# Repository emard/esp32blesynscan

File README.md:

# ESP32 blesyncscan

Micropython ESP32, ESP32S3, ESP32C3 Bluetooth Low Energy (BLE)
Motor server, WiFi Motor Server and USB-WiFi Motor Client for
SynScan Pro on Windows, Linux, Android.
Arduino ESP32 Bluetooth Classic UART bridge for SynScan Pro
under Wine on Linux.
UART 3.3V TTL is connected to SkyWatcher Virtuoso Mini
or Virtuoso GTi mount.

ESP32C3 USB-C port can be used as direct USB-SERIAL on PC
connected to Motor over wire or remote USB-SERIAL over WiFi.

Do not use this to upgrade Motor firmware.
Motor firmware should be upgraded over wire using
USB-SERIAL UART 3.3V TTL based on PL2303 or FT232R chip.

# Install

"micropython" directory contains latest developent.
To install, continue with micropython/README.md

"Arduino" directory contains old code which should be
upgraded with features micropython code has.
To install, continue with Arduino/README.md

Bluetooth Classic is available only for Arduino.
Micropython doesn't support Bluetooth Classic.

# Electrical

There should be 12V->3.3V converter.
To save power recommended is switching converter 
(Canton Power or RECOM).
RJ-12 plug can't guarantee that GND makes
connection before 12V pin. Hot-plugging
can apply 12V to 3.3V pins and risk a
permanent damage. Avoid hot-plugging.

On the mount "Virtuoso Mini" RX and TX are labeled
swapped and seems as wired together making it a
half-duplex serial port and ESP32 should cancel echo.
ESP32 TX line should "simulate" open collector
output with a resistor 10k and small low drop diode
BAT42.

On the mount "Virtuoso GTi" RX and TX are labeled
normal and are not wired together making it a
full-duplex serial port without echo.
ESP32 TX line should connect directly to ESP32.

In the mount manual see RJ-12 pinout.
Conenct RJ-12 RX/TX with short straight
RJ-12 cable to ESP32 RX2/TX2 pins.

# Schematics

First prototype (ESP32)

                 Canton Power
                ┌─────────────┐
                │IN        OUT│
                │12V  GND 3.3V│
                └─────────────┘
                  │    │    │
      MOUNT       │    │    └───────────────┐
     MINI/GTi     │    │                    │   ESP32
    ┌───────┐     │    │                    │  ┌───────┐
    │    12V│─────┘    │         10k/BAT42  └──│3.3V   │
    │       │          │         ┌─░░░░─┐      │       │
    │     TX│──────────│─────────┼──>∫──┴──────│TXD    │
    │       │          │         └─────────────│TX     │
    │     RX│──────────│───────────────────────│RX     │
    │       │          │                       │       │
    │    GND│──────────┴───────────────────────│GND    │
    └───────┘                                  └───────┘

Minimal schematic (ESP32S3) old

                     RECOM
                 R-78K3.3-0.5
                ┌─────────────┐
                │12V  GND 3.3V│
                │IN        OUT│
                └─────────────┘
                  │    │    │
      MOUNT       │    │    └─────────┐
     MINI/GTi     │    │              │   ESP32S3
    ┌───────┐     │    │              │  ┌───────┐
    │    12V│─────┘    │   10k/BAT42  └──│3.3V   │
    │       │          │    ┌─░░░░─┐     │       │
    │     TX│──────────│────┼──>∫──┴─────│TXD    │
    │       │          │    └────────────│TX     │
    │     RX│──────────│─────────────────│RX     │
    │       │          │                 │       │
    │    GND│──────────┴─────────────────│GND    │
    └───────┘                            └───────┘

Minimal schematic (ESP32S3) new

                     RECOM
                 R-78K3.3-0.5
                ┌─────────────┐
                │12V  GND 3.3V│
                │IN        OUT│
                └─────────────┘
                  │    │    │
      MOUNT       │    │    └─────────┐
     MINI/GTi     │    │              │   ESP32S3
    ┌───────┐     │    │   10k/BAT42  │  ┌───────┐
    │    12V│─────┘    │    ┌─░░░░─┐  └──│3.3V   │
    │       │          │    ├──>∫──┴─────│TXD    │
    │     TX│──────────│────┴────────────│TX     │
    │       │          │    ┌─░░░░─┐     │       │
    │     RX│──────────│────┼──>∫──┴─────│RXD    │
    │       │          │    └────────────│RX     │
    │    GND│──────────┴─────────────────│GND    │
    └───────┘                            └───────┘

part numbers and pinouts

    RJ-11 or RJ-12 Connector
    Mouser P/N: 538-95501-2661   0.5$
    Mouser P/N: 523-RJE031660310 1$
    Mouser P/N: 490-CRJ051-1-TH  2$

      RJ-12         RJ-11
    ┌────────┐    ┌────────┐
    │ 123456 │    │  2345  │
    │        │    │        │
    └──┐  ┌──┘    └──┐  ┌──┘
       └──┘          └──┘
    front view    front view

    1        N.C.
    2 yellow TX       (3.3V) (esp32 sends to "Mini", receives from "GTi")
    3 green  Vpp+     ( 12V) (esp32 draws power)
    4 red    RX       (3.3V) (esp32 receives from "Mini", sends to "GTi")
    5 black  GND
    6        N.N.

    Voltage converter 4.5-36V -> 3.3V
    Mouser P/N: 919-R-78K3.3-0.5 7$

                     RECOM 
                 R-78K3.3-0.5
                ┌─────────────┐
             IN │12V  GND 3.3V│ OUT
                │             │
                │             │
                └─────────────┘
                  bottom view

    XIAO ESP32S3 MINI old
    Mouser P/N: 713-113991114    7$

                 XIAO  ESP32S3
                ┌─────────────┐
                │1    USB   5V│
                │2         GND│
                │3        3.3V│
                │4           9│
                │5           8│
                │6  TX       7│
                │43 TXD  RX 44│
                └─────────────┘
                    top view

    XIAO ESP32C3 MINI old
    Mouser P/N: 713-113991054    5$

                 XIAO  ESP32C3
                ┌─────────────┐
                │2    USB   5V│
                │3         GND│
                │4        3.3V│
                │5          10│
                │6           9│
                │7  TX       8│
                │21 TXD  RX 20│
                └─────────────┘
                    top view

    XIAO ESP32S3 MINI new
    Mouser P/N: 713-113991114    7$

                 XIAO  ESP32S3
                ┌─────────────┐
                │1    USB   5V│
                │2         GND│
                │3        3.3V│
                │4           9│
                │5           8│
                │6  TXD  RXD 7│
                │43 TX   RX 44│
                └─────────────┘
                    top view

    XIAO ESP32C3 MINI new
    Mouser P/N: 713-113991054    5$

                 XIAO  ESP32C3
                ┌─────────────┐
                │2    USB   5V│
                │3         GND│
                │4        3.3V│
                │5          10│
                │6           9│
                │7  TXD  RXD 8│
                │21 TX   RX 20│
                └─────────────┘
                    top view

# Connection

Looking at female RJ-12 socket on the mount:

    ┌────────┐
    │ 123456 │
    │        │
    └──┐  ┌──┘
       └──┘

    1 blue   N.C.
    2 yellow TX       (3.3V) (mount "Mini" receives, "GTi" sends)
    3 green  Vpp+     ( 12V) (mount provides power)
    4 red    RX       (3.3V) (mount "Mini" sends, "GTi" receives)
    5 black  GND
    6 white  Reserved (3.3V)

RX/TX roles on the mount "Virtuoso Mini" are swapped and
actually indicate RX2/TX2 on ESP32.

    Virtuoso Mini  ESP32
    -------------  ----------
    2 yellow TX    TX2 GPIO17 (over resistor/diode)
    4 red    RX    RX2 GPIO16
    5 black  GND   GND

RX/TX roles on the mount "Virtuoso GTi" are labeled normal,
here we swap TX2/RX2 on ESP32.

    Virtuoso GTi   ESP32
    ------------   ----------
    2 yellow TX    RX2 GPIO17 (direct)
    4 red    RX    TX2 GPIO16
    5 black  GND   GND

RJ-11 4-pin socket can be used instead of
RJ-12 6-pin because pins 1 and 6 are not connected.

# WARNING WARNING WARNING

RJ12 pinout on the adapter matches the pinout
on the mount, so the "straight" wired cable
should be used.

There are different RJ-11 and RJ-12 cables,
with [straight and cross wiring](/doc/straight-vs-cross-cable.pdf).
For the telephones it does not matter but here it matters!

STANDARD PHONE CROSS CABLE MAY NOT BE SUITABLE.
USE ONLY STRAIGHT WIRED 4-PIN RJ-11 or
STRAIGHT WIRED 6-PIN RJ-12. CROSS RJ-11 AND RJ-12 
CABLES AND ALL 2-PIN RJ-11 CABLES ARE NOT SUITABLE.
IF A CROSS WIRED CABLE OR ANY 2-PIN CABLE IS CONNECTED
THEN 12V WILL FRY ELECTRONICS IN THE MOUNT AND ESP32.

# Bluetooth Classic or Low Energy

After board power ON or reset by pressing "EN" button,
blue LED will turn ON for 1.5 seconds.

By default if nothing is pressed ESP32 provides
Bluetooth Low Energy Serial.

If "BOOT" button is held during blue LED is ON
then ESP32 will provide Bluetooth Classic Serial.

ESP32 in Bluetooth Low Energy mode only supports
BLE protocol and does not save battery power.
In both Classic and Low Energy modes ESP32 consumes
about 70 mA.

# Android

Synscan works in BLE mode.

SynScan pro -> Settings -> Connection Settings -> BLE

If device no longer appears in connect list and 
you want to retry connecting, then android application
has to be stopped and started again:

View applications as smaller windows. To stop SynScan,
drag it left on ardoid 10 or drag it up on android 14.

Protocol testing:

"Serial Bluetooth Terminal" can connect in
Bluetooth Classic directly when ESP32 is booted
in Bluetooth Classic mode.

"Serial Bluetooth Terminal" can connect in
Low Energy mode with long touch on SynScan_BLE device
selecting "Edit" Custom profile and then
accepting offered UUID values for Service, Read and Write.
Settings:

    Receive Newline = CR
    Send    Newline = Auto (Same as Receive)
    Send    Local Echo ( o) enabled

Basic request/response works:

    request
    :e1\r

    response
    =0210A1\r

# Linux Bluetooth Classic

Bluetooth classic works from linux and
SynScan 2.5.2 pro running under wine,
connecting as serial port.

in shell 1

    hcitool scan
    Scanning ...
            24:0A:C4:11:22:33   SynScan_BT
    rfcomm bind /dev/rfcomm0 24:0A:C4:11:22:33
    unzip synscanpro_windows_252.zip
    cd SynScanPro
    wine SynScanPro.exe
    ... wine will initialize com1 as symlink to /dev/ttyS0
    ... we must change this symlink to /dev/rfcomm0

in shell 2

    cd ~/.wine/dosdevices
    ln -sf /dev/rfcomm0 com1

in SynScan Pro window 

    ... SynScan pro -> Settings -> Connect Settings -> Serial
    ... Serial Port: COM1
    ... press top "<" touch btn then "Connect" btn will appear.
    ... touch "Connect" btn, retry few times

SynScanPro can be debugged from wine:

    winedbg --gdb SynScanPro.exe
    ...
    Wine-gdb> c

# Linux Bluetooth Low Energy

Bluetooth low energy works from linux and
SynScan 2.5.2 pro running under wine,
connecting as serial port.

It works over ble-serial if esp32 is emulating
BLE nRF chip. RN4871 chip emulation will not be
detected by ble-serial.

Install
    
    https://github.com/Jakeler/ble-serial

in shell 1

    source ble-venv/bin/activate
    ble-scan -i hci1
            24:0A:C4:11:22:33   SynScan_BLE
    ble-serial -i hci1 -d 24:0A:C4:11:22:33
    (ble-venv) guest@nuc1:~$ ble-serial -i hci1 -d 24:0A:C4:11:22:33
    23:38:03.521 | INFO | linux_pty.py: Port endpoint created on /tmp/ttyBLE -> /dev/pts/2
    23:38:03.521 | INFO | ble_interface.py: Receiver set up
    23:38:03.741 | INFO | ble_interface.py: Trying to connect with 24:0A:C4:11:22:33: SynScan_BLE
    23:38:05.443 | INFO | ble_interface.py: Device 24:0A:C4:11:22:33 connected
    23:38:05.443 | INFO | ble_interface.py: Found write characteristic 6e400002-b5a3-f393-e0a9-e50e24dcca9e (H. 44)
    23:38:05.443 | INFO | ble_interface.py: Found notify characteristic 6e400003-b5a3-f393-e0a9-e50e24dcca9e (H. 41)
    23:38:05.826 | INFO | main.py: Running main loop!

in shell 2

    cd SynScanPro
    wine SynScanPro.exe
    ... wine will initialize com1 as symlink to /dev/ttyS0
    ... we must change this symlink to /dev/rfcomm0

in shell 3

    cd ~/.wine/dosdevices
    ln -sf /tmp/ttyBLE com1

in SynScan Pro window 

    ... SynScan pro -> Settings -> Connect Settings -> Serial
    ... Serial Port: COM1
    ... press top "<" touch btn then "Connect" btn will appear.
    ... touch "Connect" btn, retry few times

SynScanPro can be debugged from wine:

    winedbg --gdb SynScanPro.exe
    ...
    Wine-gdb> c

# Windows

With suitable BLE adapter, for example TP-LINK UB500
SynScan pro 2.5.2 for windows connects with "SynScan_BLE".

"SimplySerial" is simple terminal emulator for
windows. It can can be started from powershell
to print debug messages from esp32.

    ./ss -com:8 -baud:9600
    Connected
    Disconnected

# Principle of operation

ESP32 creates a bluetooth server with serial port bridge.
Phyisical TTL serial port should be 9600,8,n,1. Using 9800
baud seems to receive less noise than 9600 baud.

Minimum that works is a BLE Service (UUID 0xA002) with
two characteristics, one for RX other for TX:

RX Direction SynScan->motor (UUID 0xC302)

Bluetooth LE packetizes serial protocol so
entire message is delivered in one packet.
ESP32 filters out some problematic commands for
"2.16.A1" motor firmware (see Firmware bugfix)
other firmwares may not need it.
Message is written to TTL serial and signaled
with "NOTIFY" flow control.

TX Direction motor->SynScan (UUID 0xC306)

TTL serial receiver buffers bytes until "complete"
message is received, it begins with '=' or '!'
and ends with '\r'. It is delivered via bluetooth
and signaled with "INDICATE" flow control.

# TTL Serial Port

Mount's serial TTL port is half-duplex
and it seems that mount has hardware
loopback. So everything that esp32 sends
to the mount, the mount immediately echoes it.

In the code there is echo cancellation built in
to reduce BLE traffic, run faster and save energy.

Mount and ESP32 cannot send at the
same time. If ESP32 tries to send
while mount sends, then the data
received by ESP32 will be just noise.

Received bytes are occasionaly wrong
with typically one of the bits that
should be 0 errorenously received as 1.
This happens less often when mount is
just powered one and more often after
alignment when mount is driving motors
for tracking.

# Firmware bugfix

Motor firmware version 2.16.A1 is the latest but has
problem with SynScan application on android.
After each connect user must enable "Auxiliary Encoder"
otherwise mount will start turning around azimuth axis
and will never stop by itself (user should press cancel to stop).

According to
[BDN at Cloudy Nights](https://www.cloudynights.com/topic/941083-skywatcher-heritage-90-virtuoso-synscan-pro-compatibility/)
this bug can be fixed by making USB-SERIAL adapter and flashing firmware
[MC006_Tracking_V0216.MCF](https://stargazerslounge.com/topic/336944-firmware-for-the-virtuoso-skywatcher/)
posted by Antoine1997 at Stargazer's Lounge.

Although this firmware also has version 2.16.A1 it
is different and fixes the encoders problem. Warning
flashing firmware using WiFi dongle will brick the board and
should never be tried, so use only usb-serial.

If you are not comfortable with flashing the firmware,
here is the fix that forces using Auxiliary encoders.

fix#1: in function "udpcb()" one message is rewritten
with this fix Auxiliary Encoder doesn't have to be enabled.
It seems that mount internally always uses Auxiliary Encoders.
Regardless of Auxiliary Encoders being set ON or OFF without
this patch, when clutches are released and mount is manually moved,
SynScan always knows its new position.

    :W2050000\r -> :W2040000\r

fix#2: prevents sending junk to motor firmware which
is easy to crash.

SynScan sends some AT command probably for its
original SynScan WiFi ESP8266 AT firmware.
This AT command should not reach motor firmware so
"udpcb()" function rewrites this AT command as ":e1\\r"
and to this command motor firmware responds with
version number which is not really response to AT
command but SynScan accepts it.

    AT+CWMODE_CUR?\r\n -> :e1\r

fix#3: receive buffer is discarded after timeout of 10 ms
or when unexpected (noise) byte is received outside of
expected chars "=0123456789ABCDEF!\r". Synscan will
retry the command after its own timeout.
This fix improves initial connect, without this fix
and without open collector fit with diode and resistor,
SynScan sometimes needs to be manually restarted few
times to connect.

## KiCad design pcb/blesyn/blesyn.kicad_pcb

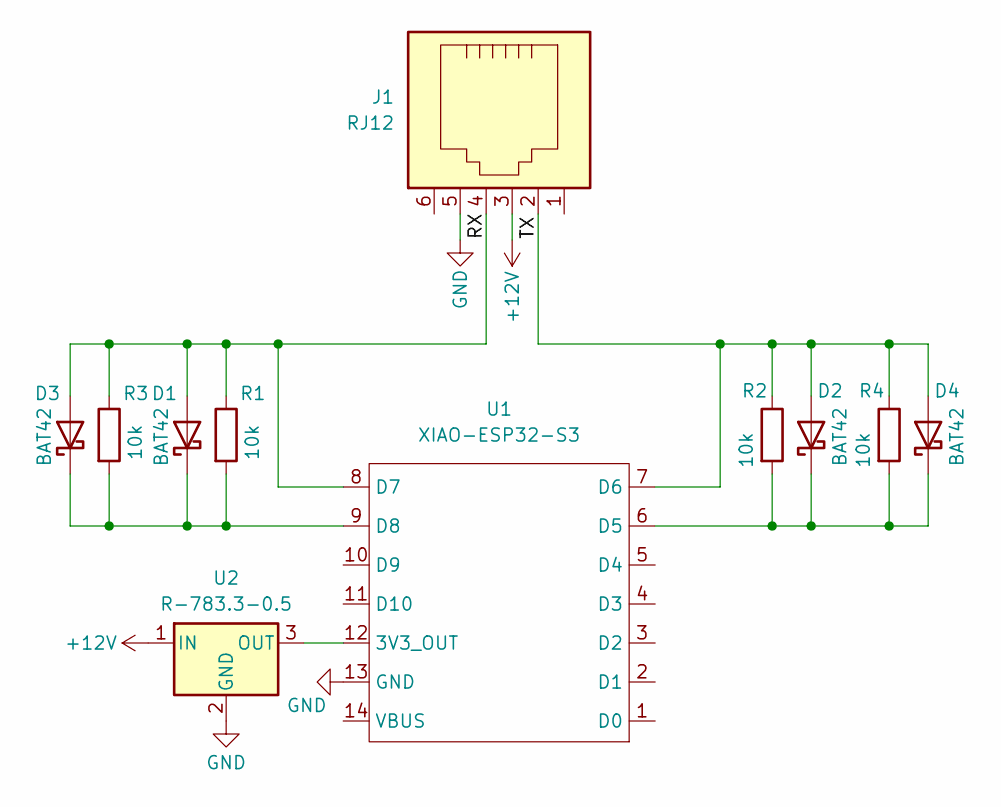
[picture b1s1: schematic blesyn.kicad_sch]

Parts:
D1, D2: BAT42; D_DO-34_SOD68_P7.62mm_Horizontal
D3, D4: BAT42; D_1206_3216Metric_Pad1.42x1.75mm_HandSolder
J1: RJ12; RJ12_Amphenol_54601-x06_Horizontal
R1, R2: 10k; R_Axial_DIN0207_L6.3mm_D2.5mm_P10.16mm_Horizontal
R3, R4: 10k; R_1206_3216Metric_Pad1.30x1.75mm_HandSolder
U1: XIAO-ESP32-S3; XIAO-ESP32-S3-DIP
U2: R-783.3-0.5; Converter_DCDC_RECOM_R-78E-0.5_THT

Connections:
+12V: J1.3, U2.1 (IN)
/RX: D1.2 (A), D3.2 (A), J1.4, R1.1, R3.1, U1.8 (D7)
/TX: D2.2 (A), D4.2 (A), J1.2, R2.1, R4.1, U1.7 (D6)
GND: J1.5, U1.13 (GND), U2.2 (GND)
unnamed: D1.1 (K), D3.1 (K), R1.2, R3.2, U1.9 (D8)
unnamed: D2.1 (K), D4.1 (K), R2.2, R4.2, U1.6 (D5)
unnamed: U1.12 (3V3_OUT), U2.3 (OUT)

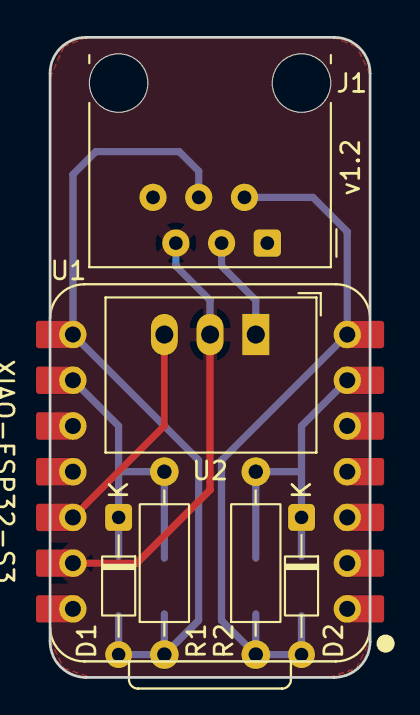
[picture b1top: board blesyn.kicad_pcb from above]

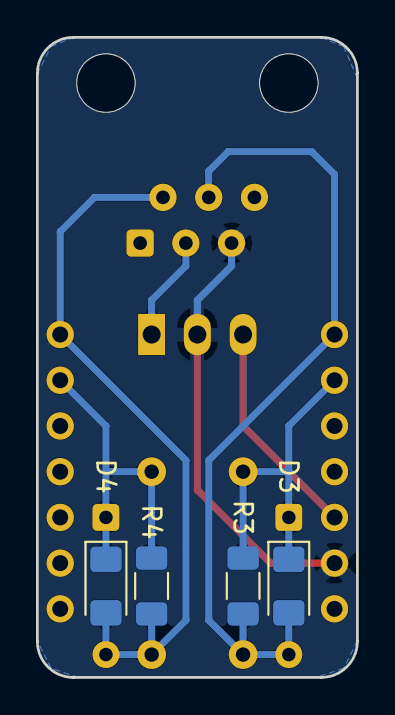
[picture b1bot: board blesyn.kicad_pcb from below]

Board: 2 copper layers, 17.8 x 35.6 mm, 11 parts (4 on the bottom side), 7 nets.

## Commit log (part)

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2024-11-09 it works from android serial terminal but synscan won't connect to this
2024-11-09 blink LED
2024-11-09 simplified blinking
2024-11-09 cleanup and more uuid's but nothing works for synscan
2024-11-09 some comments
2024-11-09 readme
2024-11-09 configurable BLE name
2024-11-10 todo
2024-11-10 bluetooth classic version
2024-11-10 BLE name now SynScan_BLE
2024-11-10 BT classic version
2024-11-10 blinking
2024-11-10 BT name now "SynScan_BT"
2024-11-10 boot selectable BT or BLE serial. BT is default and it works from linux. BLE doesn't work yet for SynScan pro android.
2024-11-10 power
2024-11-14 readme BLE windows
2024-11-18 android synscan pro 2.5.2 shows device name "SynScan_BLE" in the list but doesn't connect.
2024-11-18 comments about manufacturerdata
2024-11-18 single uuid works from android's "Serial Bluetooth Terminal"
2024-11-18 cleanup single uuid characteristic
2024-11-24 comments BLE how to connect with linux
2024-11-24 trying to guess uuid, no success yet
2024-11-25 swap rx tx lines, comment what they do
2024-11-26 support notify and indicated
2024-11-26 adding 2902 descriptors, adding some values without really knowing what they do
2024-11-28 commented code to advertise service uuid this line doesn't make difference in nrf connect view of device advertisement data
2024-11-28 commented example of a multibyte write
2024-11-28 one step further, write is successful and sends data to the mount, mount responds but android seems as it doesn't get the response so no connect yet.
2024-11-28 protocol seems to flow bidirectional now but still we are geting unexpected response and no connect
2024-11-28 cleanup, protocol seems to flow but no connect yet
2024-11-28 when every command starting with ":" is rewritten as ":e1" then it connects in AZ mode, but in this case mount doesn't work
2024-11-28 more comments
2024-11-28 trying to force connect by rewriting some of commands as ":e1"
2024-11-28 cleanup
2024-11-29 synscan works now
2024-11-29 cleanup, but rewrite of AT seems not yet working
2024-11-29 fix AT rewrite, typo in multiple if/else
2024-11-29 readme, default is BLE mode
2024-11-29 small comments and debug prints
2024-11-29 boards manager
2024-11-29 compiled binary
2024-11-29 readme, android first
2024-11-29 more readme, openscad project for 3D printable box
2024-11-29 readme note about how to retry connecting on android synscan
2024-11-30 cleanup old code, comment to compile CPU frequency of 80 MHz for power saving.
2024-11-30 readme connecting with Bluetooth Serial Terminal
2024-11-30 after connect/disconnect reset BLE connection tracking states
2024-12-01 reset BLE receive buffer on timeout 10 ms
2024-12-01 filter out only acceptable chars uart seems to often send garbled data with some bits having tendency to become 1 instead of 0. Maybe weak electrical signal?
2024-12-01 board pic's
2024-12-01 readme pictures of the board
2024-12-01 binary updated
2024-12-01 readme about internal TTL serial loopback
2024-12-01 readme serial loopback, echo and noise.
2024-12-01 readme protocol fixes listed
2024-12-01 typos readme
2024-12-01 noise reduction options and seems 9800 baud works slightly more reliable than 9600
2024-12-07 revert speed to 9600 after putting schottky diode BAT42 in series with TX. This diode simulates open collector TX.
2024-12-08 schematics
2024-12-08 simple diode symbol maybe renders better
2024-12-08 note a bit old pics
2024-12-08 readme schematics updated with 10k pullup to 3.3V
2024-12-12 esp32-s3 version, visible on BLE list but untested
2024-12-21 xiao_esp32s3: source compiles but untested
2024-12-21 readme preparation for ESP32S3
2024-12-21 RJ12 socket turned around now it is in the same position as on the mount
2024-12-21 ESP32S3 schematics
2024-12-21 readme schem cleanup
2024-12-22 usb-serial bridge, works for linux wine synscan doesn't work for android
2024-12-22 esp32s3 3D printable box
2024-12-22 create esp32 directory and move projects there
2024-12-22 readme cleanup, update for ESP32S3
2024-12-22 cleanup readme
2024-12-22 readme simplyfied ESP32S3 schematics
2024-12-22 readme aboud USB-SERIAL wired connection.
2024-12-22 esp32 usb-serial, works on linux wine synscan doesn't work on android
2024-12-22 better rails for esp32s3 box
2024-12-22 usb-serial at the same time as BLE
2024-12-22 box for RJ-12 connector top socked (hole on box side)
2024-12-22 expect find firmware version, for specific value "=0210A1\r" apply bugfix rewriting aux encoder command
2024-12-22 easier insertion, allow space for solder points
2024-12-23 readme update filter noise and reconnect
2024-12-23 BLE LED disconnected: blink, connected: on
2024-12-23 compile time option "CANCEL_ECHO", rename "NOISE_REDUCTION" -> "VALID_CHARS_ONLY" self-descriptive
2024-12-23 usb-serial in the same loop as BLE. currently packet rewriting is not done for usb-serial. usb-serial on linux wine works ok.
    usb-serial on android connects but it is unreliable,
    data garbled, probably collistions doing TX while RX.
2024-12-23 increase silence 1->2us but android usb-serial is still unreliable. todo: buffer whole packet and send after "\r" is received
2024-12-23 trying to fix android usb-serial, still not ok
2024-12-24 usb-serial rxbuf with rewriting
2024-12-24 VALID_CHARS_ONLY apply for rxbuf
2024-12-24 trying to fix android usb-serial with timeouts but still garbage in serial
2024-12-24 present release, android usb-serial not working good
2024-12-25 usbserial example, works for linux wine synscan doesn't work for android
2024-12-25 various tricks applied trying to fix protocol for android but not much can be done. Best option is to disable throttling cancel echo and let only packets with valid chars pass
2024-12-27 RJ-12 RJ-11 sockets part numbers
2024-12-27 connector pinout
2024-12-27 esp32 TX/RX signal direction
2024-12-27 12V power direction indicated
2025-01-02 pic of esp32s3
2025-01-14 micropython version
2025-01-14 readme and simple main.py file
2025-03-24 binary release
2025-03-25 binary esp32 esp32s3
2025-07-02 micropython: slow speed option is 5V friendly
2025-07-02 esp32s3: 5V friendly and quiet: limit speed from 9 to 8
2025-07-02 esp32s3 binary
2025-07-25 instead of speed 8 use speed 8.5 a bit faster and still 5V friendly
2025-09-14 readme about editor
2025-09-14 pinouts for mini and GTi GTi currently doesn't work.
2025-09-14 readme with differences between TX/RX on Virtuoso "mini" and "GTi"
2025-09-14 python version configurable for various pinouts
2025-09-14 micropython version with config file
2025-09-14 micropython improved serial read with cancel echo
2025-09-15 micropython with serial pinout autodetection
2025-09-17 micropython allow response can start with "=" or "!" not only "="
2025-09-17 optional Virtuoso AZ encoder fix
2025-09-17 readme firmware fix
2025-09-19 micropython slow speed to prevent main encoders loosing counts
2025-09-20 micropython cleanup and prepared to add wifi udp mode
2025-09-20 rename ble registered "endpoints"
2025-09-20 micropython different speeds for main and aux encoders
2025-09-20 micropython configurable wifi/ble
2025-09-20 micropython main
2025-09-20 micropython udp server example
2025-09-20 micropython moving test examples to test dir
2025-09-21 micropythonc cleanup details limit udp tx/rx to 32 chars, blink led
2025-09-21 micropython cfg encoders 0:main/aux 1:main 2:aux
2025-09-21 micropython if e1 (get fw version) is unsuccessful, try wire_autodetect()
2025-09-21 micropython wifi timer led update
2025-09-21 wifi mode doesn't like uart audotect while trying to connect
2025-10-11 GTi: correcting wrong counts per revolution
2025-10-11 configurable dictionary replacement of commands and responses
2025-10-11 slow goto for GTi
2025-10-11 duplex autodetect bug fixed (wrong identation)
2025-10-11 print trying duplex
2025-10-11 fine tuning
2025-10-12 fine tuning to match same point goto (alt,az) from (0°,0°) to (180°,180°) and back
2025-10-12 print AT commands for debugging
2025-10-12 fine tuning and code cleanup
2025-10-12 slow down manual slew
2025-10-12 cleanup comments
2025-10-12 help line in main
2025-10-12 allow to rewrite response of firmware version
2025-10-12 UDP 256 UDP packet len limit for new X-commands
2025-10-12 allow max 256 bytes for serial response
2025-10-12 udp connecting successful with X-commands
2025-10-12 set RX buffer size to 256 bytes to allow long X-commands used by new firmware 3.40.AF and new synscan 2.6.5
2025-10-12 config with replacing new X commands
2025-10-12 recognize older firmware version
2025-10-13 config: adjust counts per revolution, set WiFi AP channel
2025-10-13 support setting WiFi AP channel
2025-10-13 wifi setting tx power
2025-10-13 default wifi channel 10
2025-10-15 reporting firmware version 2.16.A1 seems to fix aux encoders because synscan will use E and F initialization commands during connect phase
2025-10-15 typo
2025-10-15 reverting to 2.16.A1 and using E and F doesn't fix aux encoders on firmware 3.40.AF. After few minutes of woring with aux encoders mount will loose position and go "crazy"
2025-10-16 on firmware 3.40.AF replace with version 3.36.AF and it works ok
2025-10-16 readme aux encoders
2025-10-16 in readme correct 100->200 lines of micropython
2025-10-20 rewrite fw version
2025-10-26 backlash
2025-10-26 pic of motor worm wheel transmission
2025-10-26 backlash text improved
2025-10-26 baclash describe black screw
2025-11-08 2 methods to notify
2025-11-08 fine tuning 180 turn
2025-11-08 micropython support for wifi client
2025-11-08 wifi ap: print IP immediately wifi client: print IP when connected
2025-11-08 comment
2025-11-09 ble remote connection, currently only TX works, RX doesn't
2025-11-09 rename remote.py -> bleremote.py
2025-11-09 simplify
2025-11-09 wip: wifi client example, connects but doesn't work
2025-11-09 wifiremote.py example, no good results yet
2025-11-09 wifiremote.py works for esp32c3
2025-11-10 wifiremote.py cleanup
2025-11-10 input demo
2025-11-10 commented led pin for esp32 devikit
2025-11-10 esp32c3 pinout
2025-11-10 new code esp32c3 as wifi client when typing commands like :e1 it works but synscan won't connect
2025-11-10 wine connects but with serial timeout 5000 ms
2025-11-10 synscan.py simplify and cleanup
2025-11-10 synscan_cfg.py cleanup
2025-11-10 comments
2025-11-11 synscan_cfg.py
2025-11-11 WiFi server section
2025-11-11 moving files to Arduino directory and update readme's
2025-11-11 support wired usb-serial, untested
2025-11-11 synscan_cfg.py autodetect chip type
2025-11-11 synscan.py usbserial fix typo wire_txrx() -> wire_txrx_replace()
2025-11-12 pye editor help
2025-11-12 pye editor help when low memory
2025-11-12 print quick help in main.py
2025-11-12 ctrl-dccc to get prompt before synscan loads
2025-11-12 logging
2025-11-12 organize cfg file
2025-11-13 original wifi dongle sometimes sends \r at start of UDP response, cleanup it with .strip()+b"\r" linux wine synscan works with that
2025-11-13 lstrip() to remove leading "\r" which client receives from Virtuoso Mini with original WiFi dongle
2025-11-13 synscan_cfg.py example for direct wire usb-serial
2025-11-16 synscan_cfg.py with new pinouts
2025-11-16 readme with new pinouts
2025-11-16 new box for C3/S3
2025-11-16 pye help ctrl-e refresh screen
2025-11-16 micropython ESP32S3: fix to connect as client
2025-11-16 S3 fix for WiFi connect: reduce txpower=17 -> txpower=15
2025-11-16 scanscan_cfg.py cleanup
2025-11-16 wifi/ble sleep after no connection timeout
2025-11-16 link to matrix library for micropython
2025-11-16 example for matrix rotation
2025-11-16 if SLEEP=0 then don't sleep
2025-11-17 rotation
2025-11-26 test: comment note quternion rotation
2025-12-07 standalone mode: python cmd() interface: synscan.cmd(b":e1\r")
2025-12-13 reduce tx power otherwise wifi won't connect increase timeout to 2 seconds
2025-12-19 cfg example for python interface
2025-12-29 rename synscan->syn
2026-03-07 adjust full circle number of counts
2026-06-22 slow down GOTO AZ axis for MINI
